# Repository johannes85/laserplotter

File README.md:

Laserplotter
============
DIY laserplotter controlled by an Arduino

Project page:  
http://www.domestichacks.info/projekte/laserplotter/

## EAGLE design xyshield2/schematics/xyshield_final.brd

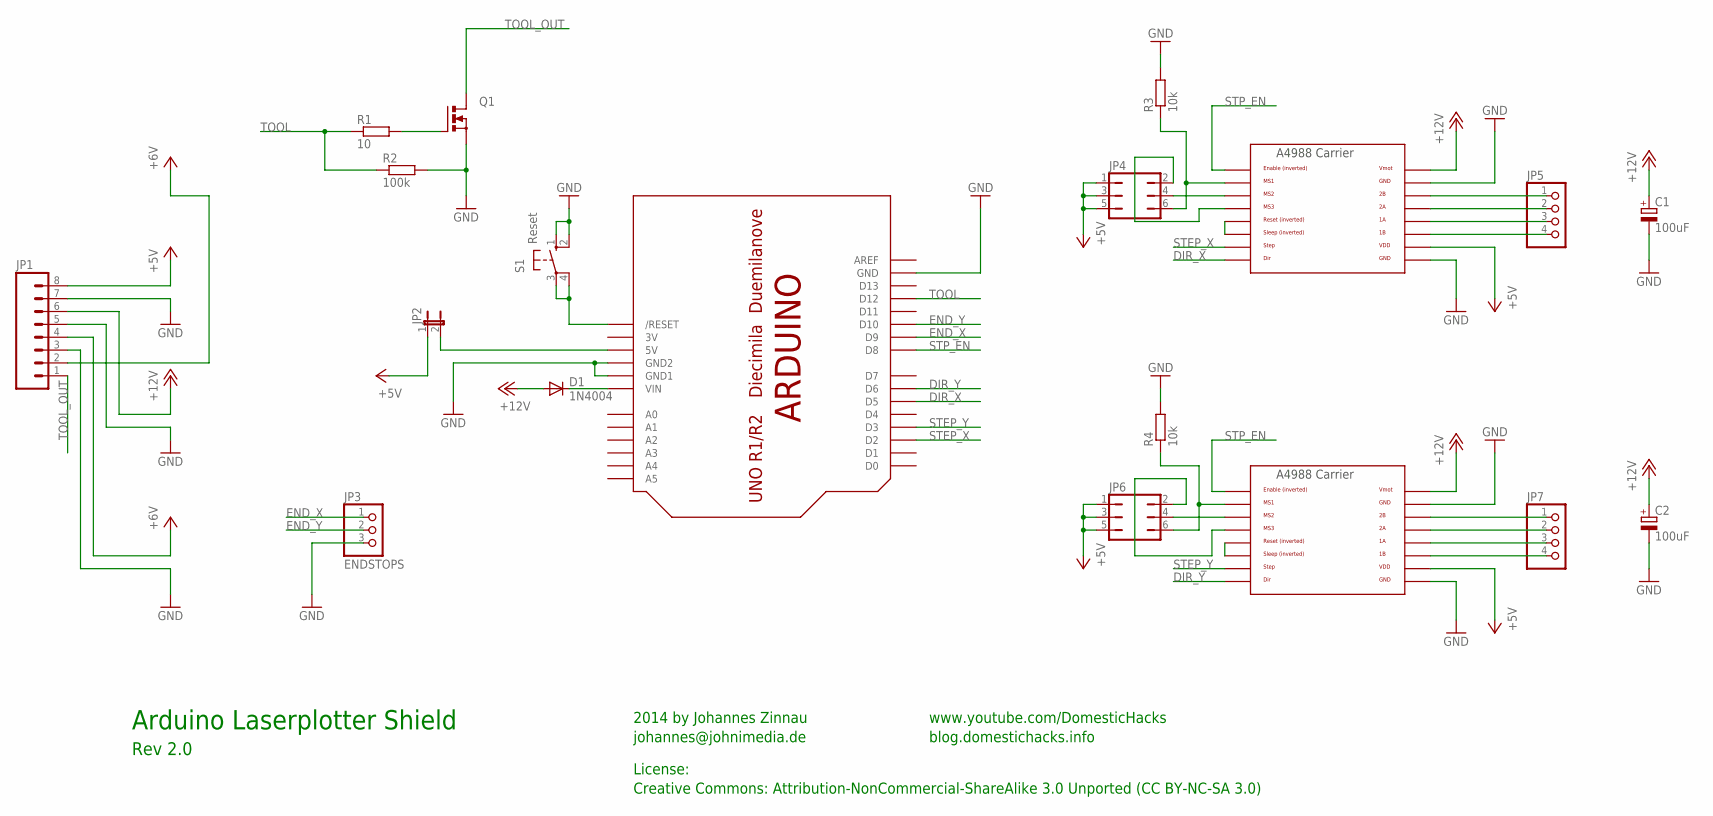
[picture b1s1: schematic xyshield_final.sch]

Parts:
C1, C2: 100uF; E2,5-6
D1: 1N4004; DO41-10
JP1: M083.5MM-8; SCREWTERMINAL-3.5MM-8
JP2: JUMPER-2PTH; 1X02
JP3: ENDSTOPS; 1X03
JP4, JP6: JP3Q
JP5, JP7: PINHD-1X4; 1X04
Q1: PMOSFET_NTO220BV; TO220BV
R1: 10; 0207/10
R2: 100k; 0207/10
R3, R4: 10k; 0207/2V
S1: Reset; B3F-10XX
U$1, U$2: POLOLU_A4983CARRIER; A4988BREAKOUT
U$3: ARDUINOUNO; ARDUINO

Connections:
3V: U$3.3V
+5V: JP1.8, JP2.1, JP4.1, JP4.3, JP4.5, JP6.1, JP6.3, JP6.5, U$1.VDD, U$2.VDD
+12V: C1.+, C2.+, D1.A, JP1.6, U$1.VMOT, U$2.VMOT
DIR_X: U$1.DIR, U$3.D5
DIR_Y: U$2.DIR, U$3.D6
END_X: JP3.1, U$3.D9
END_Y: JP3.2, U$3.D10
GND: C1.-, C2.-, JP1.3, JP1.5, JP1.7, JP3.3, Q1.S, R2.2, R3.2, R4.2, S1.1 (S), S1.2 (S1), U$1.GND, U$1.GND@0 (GND), U$2.GND, U$2.GND@0 (GND), U$3.GND, U$3.GND1, U$3.GND2
unnamed: Q1.G, R1.2
unnamed: U$1.RST, U$1.SLP (SLEEP)
unnamed: JP5.3, U$1.1A
unnamed: JP5.2, U$1.2A
unnamed: JP5.1, U$1.2B
unnamed: JP5.4, U$1.1B
unnamed: JP4.6, R3.1, U$1.MS1
unnamed: JP4.4, U$1.MS2
unnamed: JP4.2, U$1.MS3
unnamed: U$2.RST, U$2.SLP (SLEEP)
unnamed: JP7.4, U$2.1B
unnamed: JP7.3, U$2.1A
unnamed: JP7.2, U$2.2A
unnamed: JP7.1, U$2.2B
unnamed: JP6.6, R4.1, U$2.MS1
unnamed: JP6.4, U$2.MS2
unnamed: JP6.2, U$2.MS3
unnamed: JP2.2, U$3.5V
unnamed: D1.C, U$3.VIN
unnamed: S1.3, S1.4 (P1), U$3.RESET (/RESET)
STEP_X: U$1.STEP, U$3.D2
STEP_Y: U$2.STEP, U$3.D3
STP_EN: U$1.EN, U$2.EN, U$3.D8
TOOL: R1.1, R2.1, U$3.D12
TOOL_OUT: JP1.1, Q1.D
VCC: JP1.2, JP1.4

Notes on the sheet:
Arduino Laserplotter Shield
Rev 2.0
2014 by Johannes Zinnau
johannes@johnimedia.de
www.youtube.com/DomesticHacks
blog.domestichacks.info
License:
Creative Commons: Attribution-NonCommercial-ShareAlike 3.0 Unported (CC BY-NC-SA 3.0)

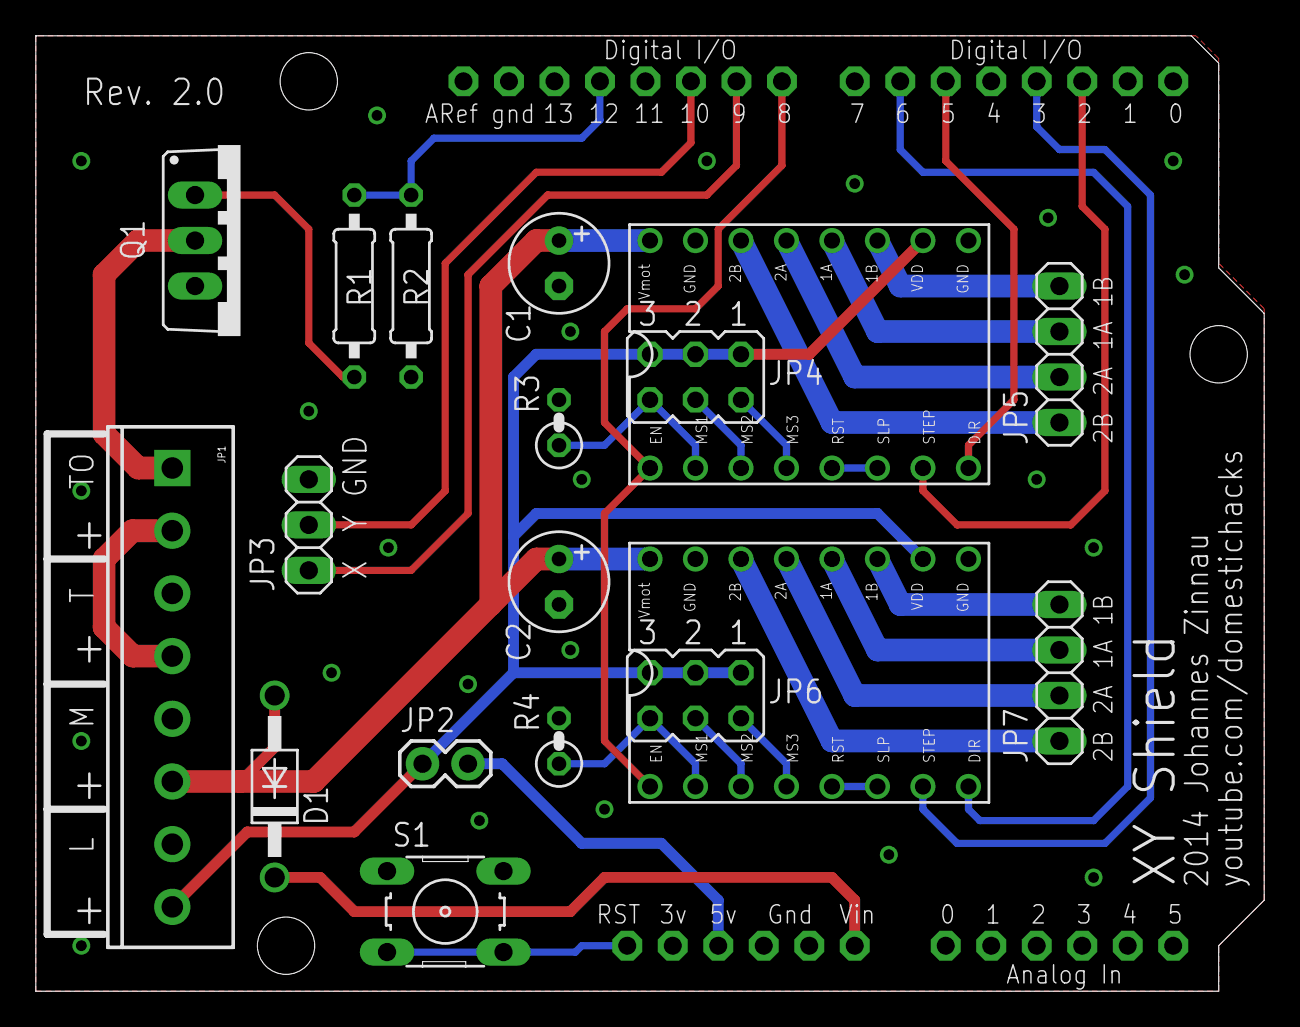
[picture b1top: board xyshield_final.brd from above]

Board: 2 copper layers, 68.6 x 53.3 mm, 19 parts (0 on the bottom side), 33 nets.

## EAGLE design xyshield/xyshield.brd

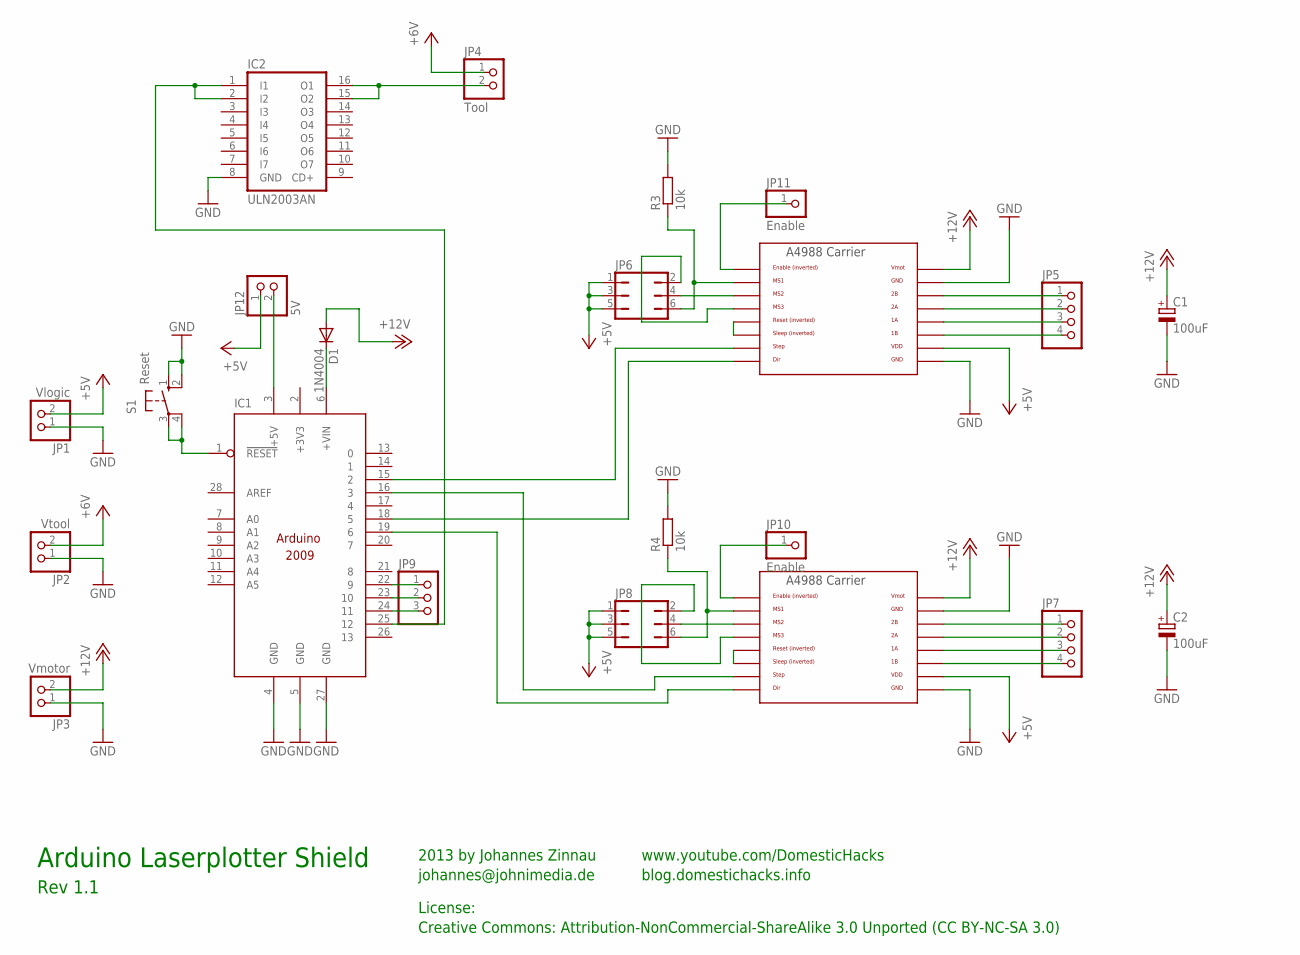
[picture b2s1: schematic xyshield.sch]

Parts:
C1, C2: 100uF; E2,5-6
D1: 1N4004; DO41-10
IC1: Arduino; ARDUINO2009
IC2: ULN2003AN; DIL16
JP1: Vlogic; 1X02
JP2: Vtool; 1X02
JP3: Vmotor; 1X02
JP4: Tool; 1X02
JP5, JP7: PINHD-1X4; 1X04
JP6, JP8: JP3Q
JP9: PINHD-1X3; 1X03
JP10, JP11: Enable; 1X01
JP12: 5V; 1X02
R3, R4: 10k; 0204V
S1: Reset; B3F-10XX
U$1, U$2: POLOLU_A4983CARRIER; A4988BREAKOUT

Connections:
+3V3: IC1.2 (+3V3)
+5V: JP1.2, JP6.1, JP6.3, JP6.5, JP8.1, JP8.3, JP8.5, JP12.1, U$1.VDD, U$2.VDD
+12V: C1.+, C2.+, D1.A, JP3.2, U$1.VMOT, U$2.VMOT
GND: C1.-, C2.-, IC1.4 (GND), IC1.5 (GND), IC1.27 (GND), IC2.8 (GND), JP1.1, JP2.1, JP3.1, R3.2, R4.2, S1.1 (S), S1.2 (S1), U$1.GND, U$1.GND@0 (GND), U$2.GND, U$2.GND@0 (GND)
unnamed: IC1.25 (12), IC2.1 (I1), IC2.2 (I2)
unnamed: IC2.15 (O2), IC2.16 (O1), JP4.2
unnamed: U$1.RST, U$1.SLP (SLEEP)
unnamed: JP5.3, U$1.1A
unnamed: JP5.2, U$1.2A
unnamed: JP5.1, U$1.2B
unnamed: JP5.4, U$1.1B
unnamed: JP6.6, R3.1, U$1.MS1
unnamed: JP6.4, U$1.MS2
unnamed: JP6.2, U$1.MS3
unnamed: U$2.RST, U$2.SLP (SLEEP)
unnamed: JP7.4, U$2.1B
unnamed: JP7.3, U$2.1A
unnamed: JP7.2, U$2.2A
unnamed: JP7.1, U$2.2B
unnamed: JP8.6, R4.1, U$2.MS1
unnamed: JP8.4, U$2.MS2
unnamed: JP8.2, U$2.MS3
unnamed: IC1.15 (2), U$1.STEP
unnamed: IC1.18 (5), U$1.DIR
unnamed: IC1.16 (3), U$2.STEP
unnamed: IC1.19 (6), U$2.DIR
unnamed: IC1.22 (9), JP9.1
unnamed: IC1.23 (10), JP9.2
unnamed: IC1.24 (11), JP9.3
unnamed: JP11.1, U$1.EN
unnamed: JP10.1, U$2.EN
unnamed: IC1.1 (!RESET), S1.3, S1.4 (P1)
unnamed: D1.C, IC1.6 (+VIN)
unnamed: IC1.3 (+5V), JP12.2
VCC: JP2.2, JP4.1

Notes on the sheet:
Arduino Laserplotter Shield
Rev 1.1
2013 by Johannes Zinnau
johannes@johnimedia.de
www.youtube.com/DomesticHacks
blog.domestichacks.info
License:
Creative Commons: Attribution-NonCommercial-ShareAlike 3.0 Unported (CC BY-NC-SA 3.0)

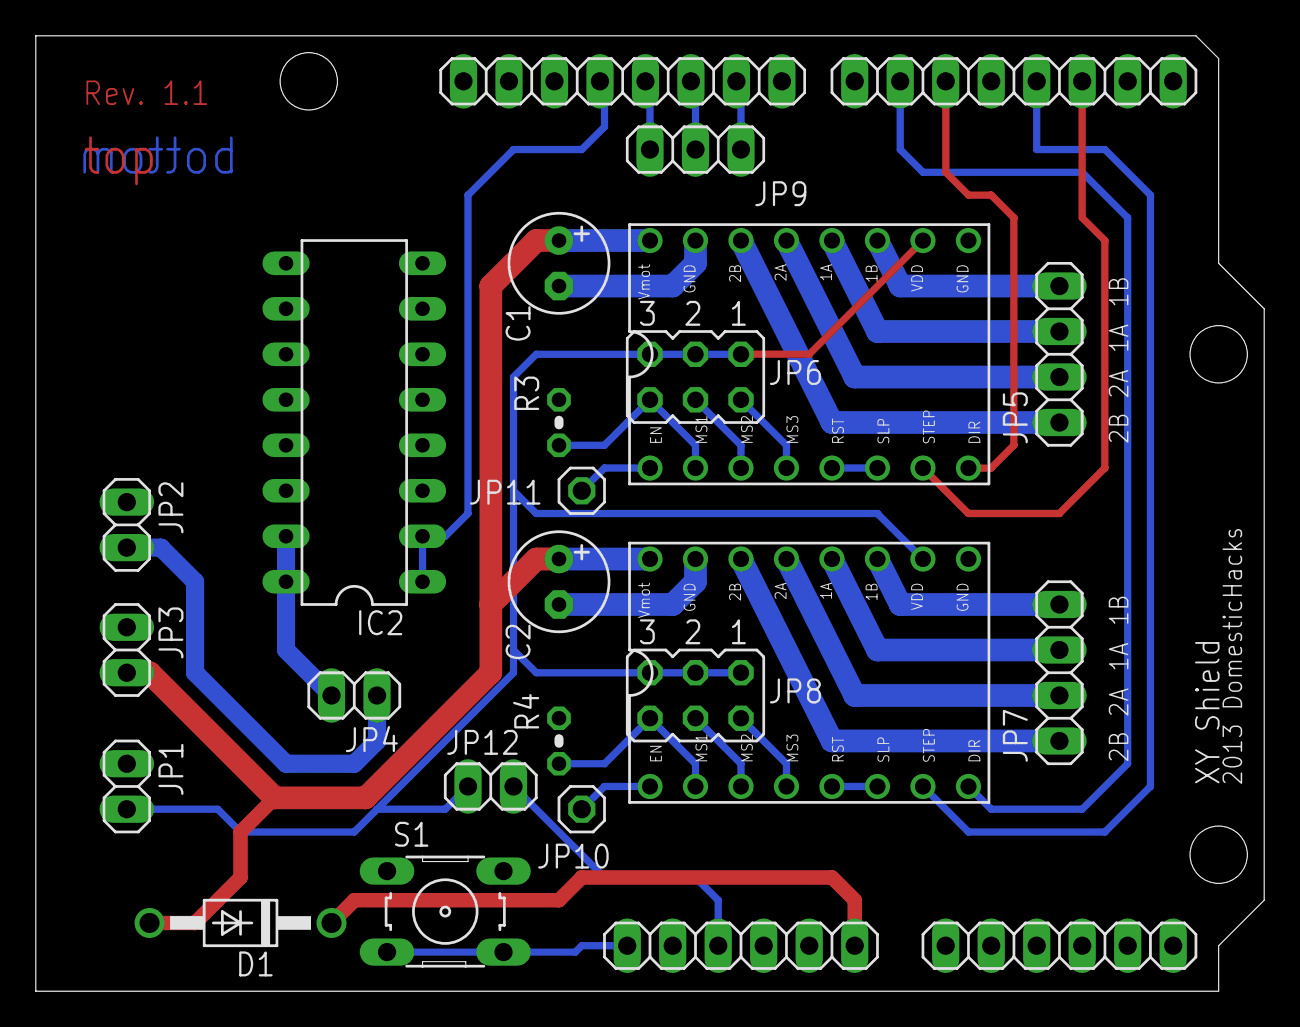
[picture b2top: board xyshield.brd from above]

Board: 2 copper layers, 68.6 x 53.3 mm, 22 parts (0 on the bottom side), 34 nets.

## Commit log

2013-12-19 Added Arduino shield schematics
2014-03-27 Board version 2
2014-03-27 Board version 2 schematics
2014-03-28 Added link to project page in readme

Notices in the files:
parts and their libraries:
SparkFun-Connectors: Licensing: CC v3.0 Share-Alike You are welcome to use this library for commercial purposes.
